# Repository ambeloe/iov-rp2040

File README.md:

# iov-rp2040
rp2040 dev board with selectable io voltages

iovdd range: 1.65v to 3.6v

PICO_FLASH_SPI_CLKDIV needs to be configured if running at 1.8V
generic boot2 needs to be used

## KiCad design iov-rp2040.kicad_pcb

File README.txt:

### iov-rp2040 ###
rp2040 dev board with selectable io voltages

iovdd range: 1.65v to 3.6v

PICO_FLASH_SPI_CLKDIV needs to be configured if running at 1.8V
generic boot2 needs to be used

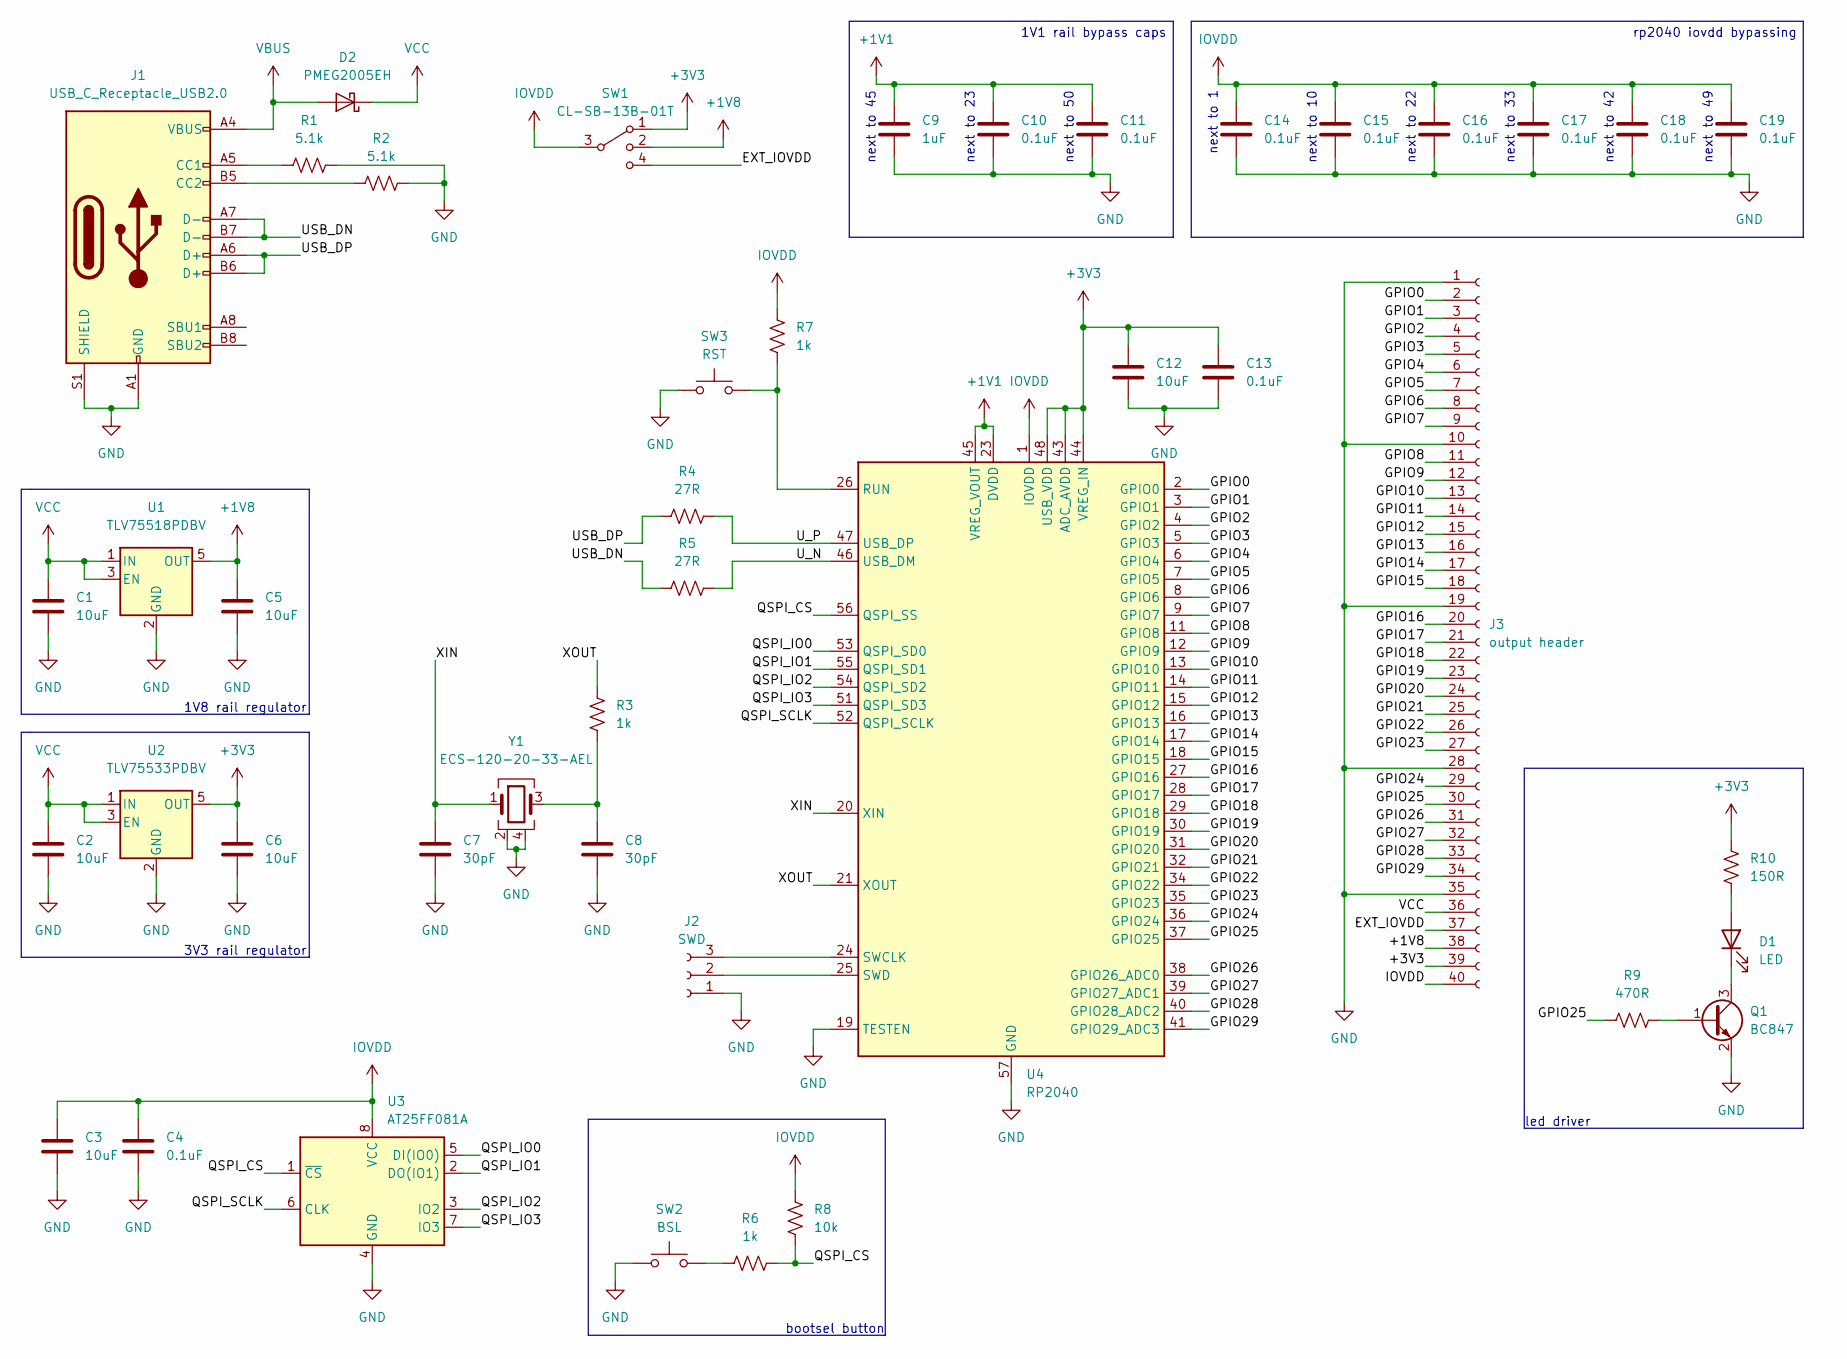
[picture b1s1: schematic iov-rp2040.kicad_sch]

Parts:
C1, C2, C3, C5, C6, C12: 10uF; C_0402_1005Metric_SmallRef
C4, C10, C11, C13, C14, C15, C16, C17, C18, C19: 0.1uF; C_0402_1005Metric_SmallRef
C7, C8: 30pF; C_0402_1005Metric_SmallRef
C9: 1uF; C_0402_1005Metric_SmallRef
D1: LED; LED_0603_1608Metric
D2: PMEG2005EH; D_SOD-123F
J1: USB_C_Receptacle_USB2.0; USB_C_Receptacle_GCT_USB4085
J2: SWD; PinHeader_1x03_P2.54mm_Vertical
J3: output header; IDC-Header_2x20_P2.54mm_Vertical
Q1: BC847; SOT-23
R1, R2: 5.1k; R_0402_1005Metric_SmallRef
R3, R6, R7: 1k; R_0402_1005Metric_SmallRef
R4, R5: 27R; R_0402_1005Metric_SmallRef
R8: 10k; R_0402_1005Metric_SmallRef
R9: 470R; R_0402_1005Metric_SmallRef
R10: 150R; R_0402_1005Metric_SmallRef
SW1: CL-SB-13B-01T
SW2: BSL; SW_SPST_EVQP2
SW3: RST; SW_SPST_EVQP2
U1: TLV75518PDBV; SOT-23-5
U2: TLV75533PDBV; SOT-23-5
U3: AT25FF081A; SOIC-8_5.275x5.275mm_P1.27mm
U4: RP2040; QFN-56-1EP_7x7mm_P0.4mm_EP3.2x3.2mm
Y1: ECS-120-20-33-AEL; Crystal_SMD_3225-4Pin_3.2x2.5mm

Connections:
+1V1: C9.1, C10.1, C11.1, U4.23 (DVDD), U4.45 (VREG_VOUT), U4.50 (DVDD)
+1V8: C5.1, J3.38, SW1.2, U1.5 (OUT)
+3V3: C6.1, C12.1, C13.1, J3.39, R10.2, SW1.1, U2.5 (OUT), U4.43 (ADC_AVDD), U4.44 (VREG_IN), U4.48 (USB_VDD)
/EXT_IOVDD: J3.37, SW1.4
/GPIO0: J3.2, U4.2 (GPIO0)
/GPIO1: J3.3, U4.3 (GPIO1)
/GPIO2: J3.4, U4.4 (GPIO2)
/GPIO3: J3.5, U4.5 (GPIO3)
/GPIO4: J3.6, U4.6 (GPIO4)
/GPIO5: J3.7, U4.7 (GPIO5)
/GPIO6: J3.8, U4.8 (GPIO6)
/GPIO7: J3.9, U4.9 (GPIO7)
/GPIO8: J3.11, U4.11 (GPIO8)
/GPIO9: J3.12, U4.12 (GPIO9)
/GPIO10: J3.13, U4.13 (GPIO10)
/GPIO11: J3.14, U4.14 (GPIO11)
/GPIO12: J3.15, U4.15 (GPIO12)
/GPIO13: J3.16, U4.16 (GPIO13)
/GPIO14: J3.17, U4.17 (GPIO14)
/GPIO15: J3.18, U4.18 (GPIO15)
/GPIO16: J3.20, U4.27 (GPIO16)
/GPIO17: J3.21, U4.28 (GPIO17)
/GPIO18: J3.22, U4.29 (GPIO18)
/GPIO19: J3.23, U4.30 (GPIO19)
/GPIO20: J3.24, U4.31 (GPIO20)
/GPIO21: J3.25, U4.32 (GPIO21)
/GPIO22: J3.26, U4.34 (GPIO22)
/GPIO23: J3.27, U4.35 (GPIO23)
/GPIO24: J3.29, U4.36 (GPIO24)
/GPIO25: J3.30, R9.1, U4.37 (GPIO25)
/GPIO26: J3.31, U4.38 (GPIO26_ADC0)
/GPIO27: J3.32, U4.39 (GPIO27_ADC1)
/GPIO28: J3.33, U4.40 (GPIO28_ADC2)
/GPIO29: J3.34, U4.41 (GPIO29_ADC3)
/QSPI_CS: R6.2, R8.2, U3.1 (~CS), U4.56 (QSPI_SS)
/QSPI_IO0: U3.5 (DI(IO0)), U4.53 (QSPI_SD0)
/QSPI_IO1: U3.2 (DO(IO1)), U4.55 (QSPI_SD1)
/QSPI_IO2: U3.3 (IO2), U4.54 (QSPI_SD2)
/QSPI_IO3: U3.7 (IO3), U4.51 (QSPI_SD3)
/QSPI_SCLK: U3.6 (CLK), U4.52 (QSPI_SCLK)
/USB_DN: J1.A7 (D-), J1.B7 (D-), R5.1
/USB_DP: J1.A6 (D+), J1.B6 (D+), R4.1
/U_N: R5.2, U4.46 (USB_DM)
/U_P: R4.2, U4.47 (USB_DP)
/XIN: C7.1, U4.20 (XIN), Y1.1
/XOUT: R3.1, U4.21 (XOUT)
GND: C1.2, C2.2, C3.2, C4.2, C5.2, C6.2, C7.2, C8.2, C9.2, C10.2, C11.2, C12.2, C13.2, C14.2, C15.2, C16.2, C17.2, C18.2, C19.2, J1.A1 (GND), J1.A12 (GND), J1.B1 (GND), J1.B12 (GND), J1.S1 (SHIELD), J2.1, J3.1, J3.10, J3.19, J3.28, J3.35, Q1.2 (E), R1.2, R2.2, SW2.1, SW3.1, U1.2 (GND), U2.2 (GND), U3.4 (GND), U4.19 (TESTEN), U4.57 (GND), Y1.2, Y1.4
IOVDD: C3.1, C4.1, C14.1, C15.1, C16.1, C17.1, C18.1, C19.1, J3.40, R7.1, R8.1, SW1.3, U3.8 (VCC), U4.1 (IOVDD), U4.10 (IOVDD), U4.22 (IOVDD), U4.33 (IOVDD), U4.42 (IOVDD), U4.49 (IOVDD)
unnamed: C8.1, R3.2, Y1.3
unnamed: D1.1 (K), Q1.3 (C)
unnamed: D1.2 (A), R10.1
unnamed: J1.A5 (CC1), R1.1
unnamed: J1.B5 (CC2), R2.1
unnamed: J2.2, U4.25 (SWD)
unnamed: J2.3, U4.24 (SWCLK)
unnamed: Q1.1 (B), R9.2
unnamed: R6.1, SW2.2
unnamed: R7.2, SW3.2, U4.26 (RUN)
VBUS: D2.2 (A), J1.A4 (VBUS), J1.A9 (VBUS), J1.B4 (VBUS), J1.B9 (VBUS)
VCC: C1.1, C2.1, D2.1 (K), J3.36, U1.1 (IN), U1.3 (EN), U2.1 (IN), U2.3 (EN)

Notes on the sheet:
bootsel button
1V1 rail bypass caps
1V8 rail regulator
led driver
next to 10
next to 42
next to 1
next to 49
next to 45
next to 23
rp2040 iovdd bypassing
next to 22
next to 50
next to 33
3V3 rail regulator

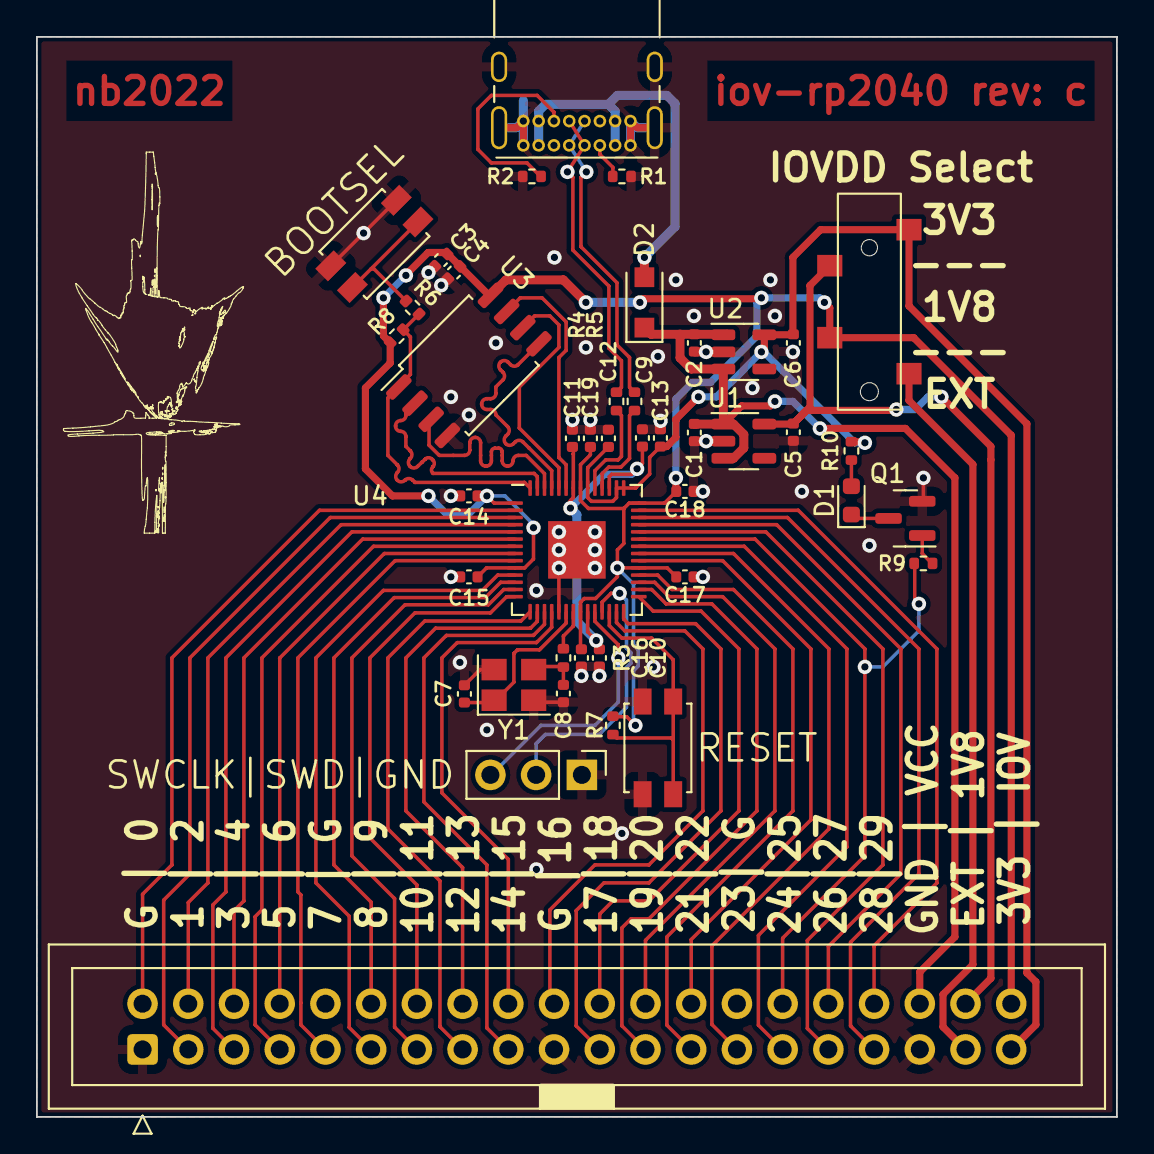
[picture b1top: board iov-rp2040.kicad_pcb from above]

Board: 2 copper layers, 60.0 x 60.0 mm, 43 parts (0 on the bottom side), 60 nets.

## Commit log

2022-08-28 initial commti
2022-08-28 fix gitignore
2022-09-06 revision b:
    fixed flash footprint
    changed ground pour to be cleaner
    added name and revision text
2022-09-06 updated bom for rev b
2022-09-12 length matched qspi and redid power section
2022-09-12 forgot rev c image
